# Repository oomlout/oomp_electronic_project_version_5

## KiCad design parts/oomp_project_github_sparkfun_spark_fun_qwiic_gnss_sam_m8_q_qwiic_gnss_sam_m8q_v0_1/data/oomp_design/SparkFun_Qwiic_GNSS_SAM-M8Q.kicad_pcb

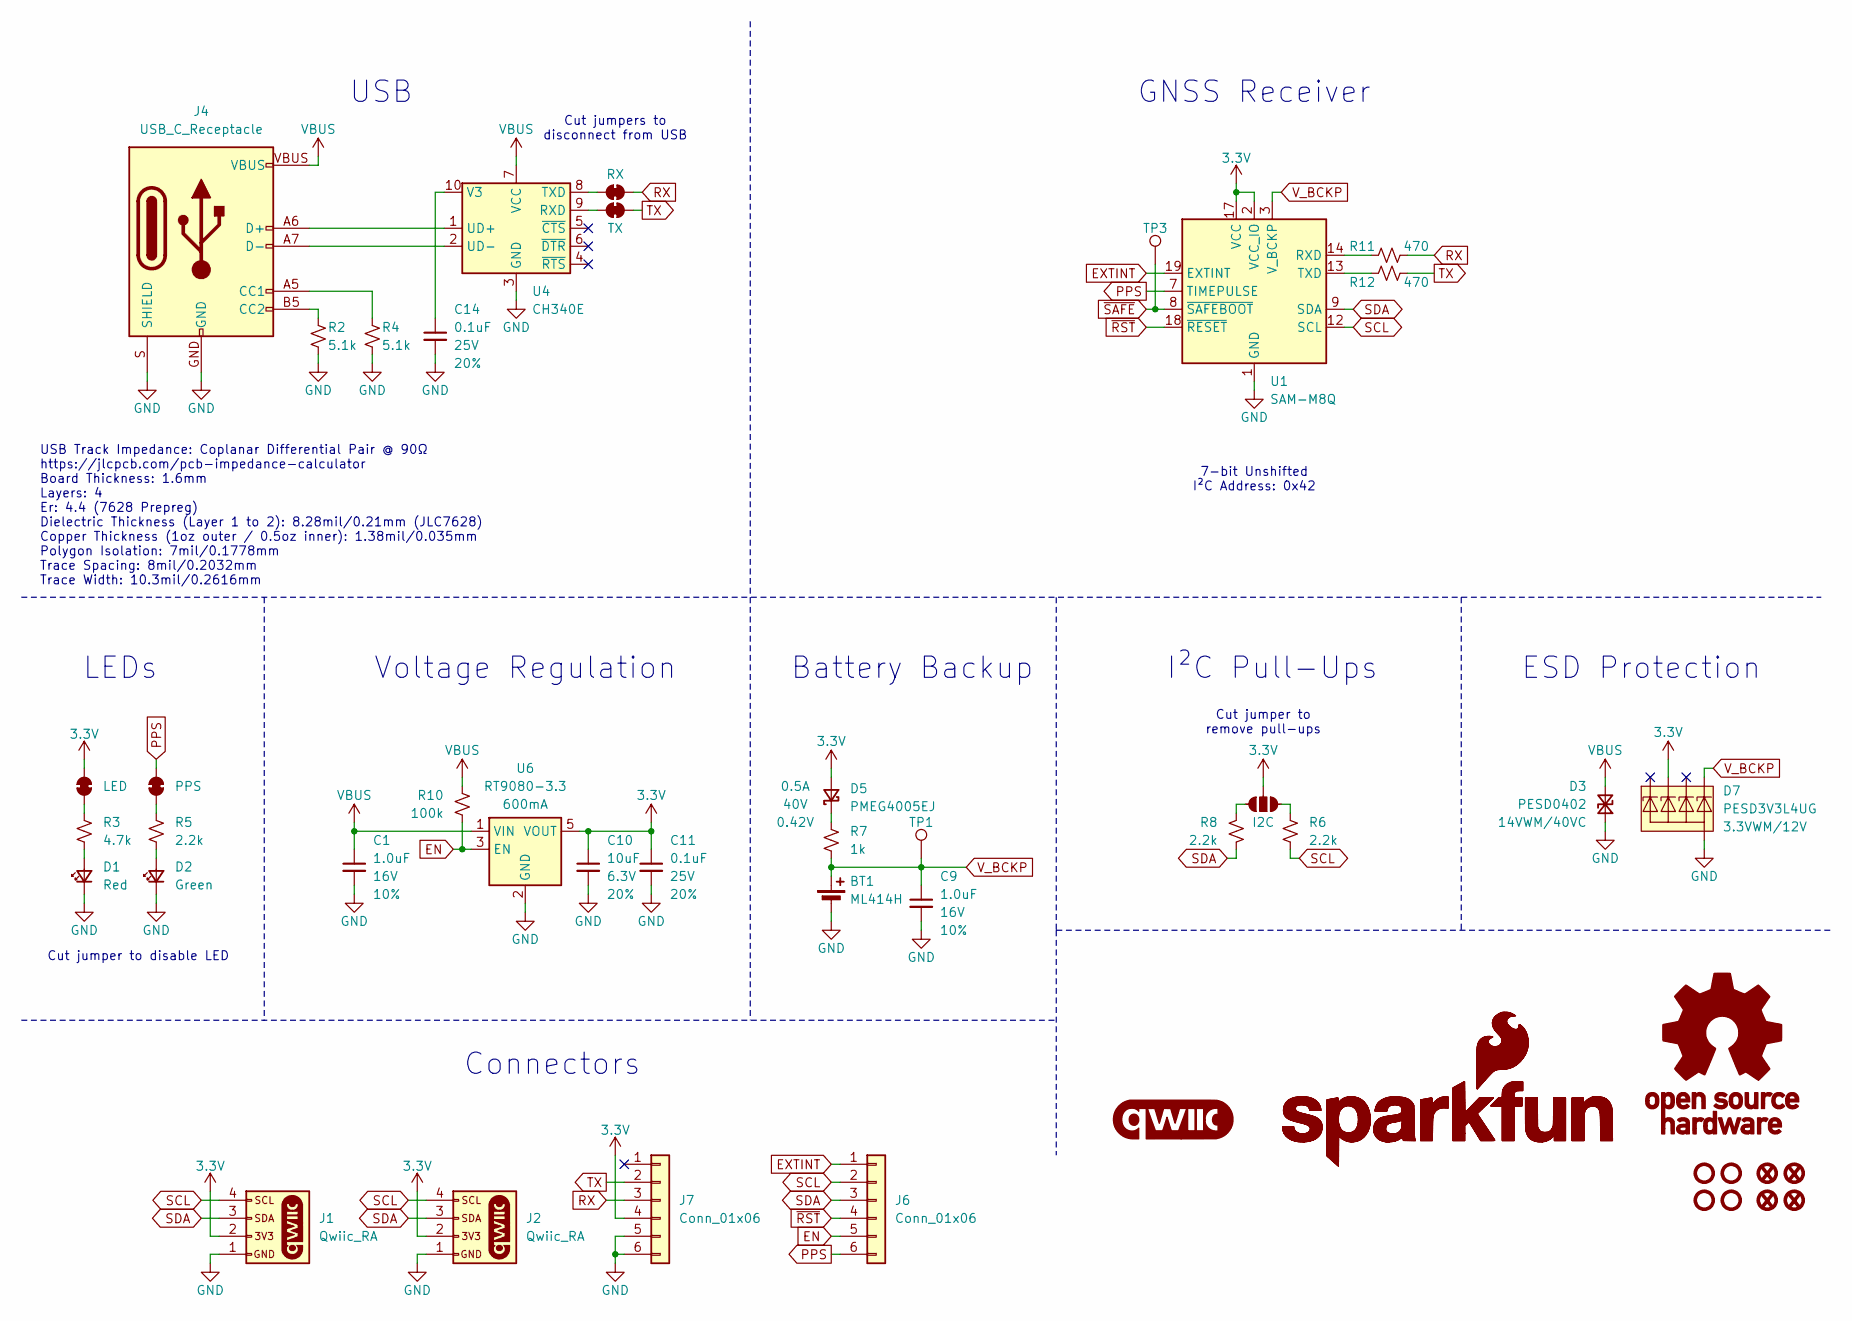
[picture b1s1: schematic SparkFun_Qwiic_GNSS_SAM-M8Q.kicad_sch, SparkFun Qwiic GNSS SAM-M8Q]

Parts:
BT1: ML414H; ML414H_IV01E
C1, C9: 1.0uF; C_0603_1608Metric; Voltage 16V; Tolerance 10%
C10: 10uF; C_0603_1608Metric; Voltage 6.3V; Tolerance 20%
C11, C14: 0.1uF; C_0603_1608Metric; Voltage 25V; Tolerance 20%
D1: Red; LED_0603_1608Metric_Red
D2: Green; LED_1206_Bottom_Green
D3: PESD0402; C_0402_1005Metric; Rating 14VWM/40VC
D5: PMEG4005EJ; SOD-323
D7: PESD3V3L4UG; SOT-353; Rating 3.3VWM/12V
FID1, FID2, FID3, FID4: Fiducial_0.5mm; Fiducial_0.5mm_Mask1mm
G1: qwiic_Logo
G2: SparkFun_Logo; SparkFun_Logo_8mm
G3: SparkFun_Logo
G4: OSHW_Logo; Creative_Commons_License
J1, J2: Qwiic_RA; JST_1x04_P1.0mm_Horizontal_SMD
J4: USB_C_Receptacle; USB-C_16
J6, J7: Conn_01x06; 1x06_P2.54mm
JP1: LED; Jumper_2_NC_Trace
JP2: I2C; Jumper_3_NO
JP3: PPS; Jumper_2_NC_Trace
JP4: RX; Jumper_2_NC_Trace
JP5: TX; Jumper_2_NC_Trace
R2, R4: 5.1k; R_0603_1608Metric
R3: 4.7k; R_0603_1608Metric
R5, R6, R8: 2.2k; R_0603_1608Metric
R7: 1k; R_0603_1608Metric
R10: 100k; R_0603_1608Metric
R11, R12: 470; R_0603_1608Metric
ST1, ST2, ST3, ST4: Standoff
TP1: TestPoint_0.75mm; TestPoint-0.75mm
TP3: 0.75mm; TestPoint-0.75mm
U1: SAM-M8Q; u-blox_SAM-M8Q
U4: CH340E; MSOP-10_3x3mm_P0.5mm
U6: RT9080-3.3; SOT23-5

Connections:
3.3V: C10.1, C11.1, D5.2 (A), D7.3 (K2), J1.2, J2.2, J7.4, JP1.2 (B), JP2.2 (B), U1.2 (VCC_IO), U1.17 (VCC), U6.5 (VOUT)
EN: J6.5, R10.1, U6.3 (EN)
EXTINT: J6.1, U1.19 (EXTINT)
GND: BT1.-, C1.2, C9.2, C10.2, C11.2, C14.2, D1.1 (K), D2.1 (K), D3.1 (A1), D7.2 (A), J1.1, J2.1, J4.GND, J4.S (SHIELD), J7.5, J7.6, R2.1, R4.1, U1.1 (GND), U1.4 (GND), U1.5 (GND), U1.6 (GND), U1.10 (GND), U1.11 (GND), U1.15 (GND), U1.16 (GND), U1.20 (GND), U4.3 (GND), U6.2 (GND)
unnamed: D1.2 (A), R3.1
unnamed: D2.2 (A), R5.1
unnamed: D5.1 (K), R7.2
unnamed: J4.A5 (CC1), R4.2
unnamed: J4.B5 (CC2), R2.2
unnamed: JP1.1 (A), R3.2
unnamed: JP2.1 (A), R6.2
unnamed: JP2.3 (C), R8.2
unnamed: JP3.1 (A), R5.2
unnamed: JP4.1 (A), U4.8 (TXD)
unnamed: JP5.1 (A), U4.9 (RXD)
unnamed: R11.1, U1.14 (RXD)
unnamed: R12.1, U1.13 (TXD)
unnamed: J4.A6 (D+), J4.B6 (D+), U4.1 (UD+)
unnamed: J4.A7 (D-), J4.B7 (D-), U4.2 (UD-)
unnamed: C14.1, U4.10 (V3)
PPS: J6.6, JP3.2 (B), U1.7 (TIMEPULSE)
RX: J7.3, JP4.2 (B), R11.2
SCL: J1.4, J2.4, J6.2, R6.1, U1.12 (SCL)
SDA: J1.3, J2.3, J6.3, R8.1, U1.9 (SDA)
TX: J7.2, JP5.2 (B), R12.2
VBUS: C1.1, D3.2 (A2), J4.VBUS, R10.2, U4.7 (VCC), U6.1 (VIN)
V_BCKP: BT1.+, C9.1, D7.5 (K4), R7.1, TP1.1, U1.3 (V_BCKP)
~RST: J6.4, U1.18 (~RESET)
~SAFE: TP3.1, U1.8 (~SAFEBOOT)

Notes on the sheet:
USB Track Impedance: Coplanar Differential Pair @ 90Ω https://jlcpcb.com/pcb-impedance-calculator Board Thickness: 1.6mm Layers: 4 Er: 4.4 (7628 Prepreg) Dielectric Thickness (Layer 1 to 2): 8.28mil/0.21mm (JLC7628) Copper Thickness (1oz outer / 0.5oz inner): 1.38mil/0.035mm Polygon Isolation: 7mil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
USB
Cut jumpers to disconnect from USB
Cut jumper to remove pull-ups
Battery Backup
I²C Pull-Ups
ESD Protection
Voltage Regulation
Cut jumper to disable LED
7-bit Unshifted I²C Address: 0x42
LEDs
Connectors
GNSS Receiver

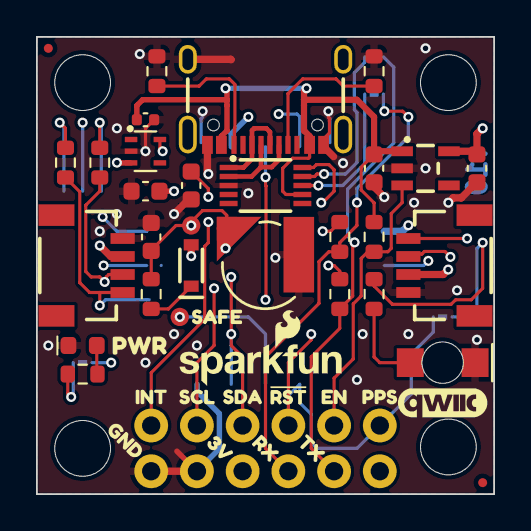
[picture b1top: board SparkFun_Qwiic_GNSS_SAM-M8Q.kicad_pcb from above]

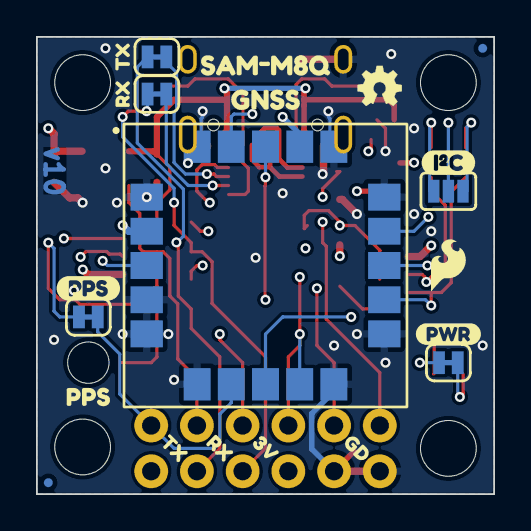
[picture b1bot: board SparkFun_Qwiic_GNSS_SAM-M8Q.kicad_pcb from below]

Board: 4 copper layers, 25.4 x 25.4 mm, 70 parts (21 on the bottom side), 29 nets.

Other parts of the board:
Ref**: Val**; OSHW_Logo_2.5mm
kibuzzard-68A62ADB: G***; kibuzzard-68A62ADB
kibuzzard-68A62B00: G***; kibuzzard-68A62B00
kibuzzard-68A543C0: G***; kibuzzard-68A543C0
kibuzzard-68A543C6: G***; kibuzzard-68A543C6
kibuzzard-68A543D0: G***; kibuzzard-68A543D0
kibuzzard-68A543D8: G***; kibuzzard-68A543D8
kibuzzard-68A5438E: G***; kibuzzard-68A5438E
kibuzzard-68A6334A: G***; kibuzzard-68A6334A
kibuzzard-68B26D79: G***; kibuzzard-68B26D79
kibuzzard-68B65C4A: G***; kibuzzard-68B65C4A
kibuzzard-68B657DC: G***; kibuzzard-68B657DC
kibuzzard-68B657F6: G***; kibuzzard-68B657F6
kibuzzard-68B657FC: G***; kibuzzard-68B657FC
kibuzzard-68B2754E, kibuzzard-68B2754E#2: G***; kibuzzard-68B2754E
kibuzzard-68B2766E: G***; kibuzzard-68B2766E
kibuzzard-68B27525, kibuzzard-68B27525#2: G***; kibuzzard-68B27525
kibuzzard-68B65800: G***; kibuzzard-68B65800
kibuzzard-68B65805: G***; kibuzzard-68B65805
kibuzzard-68F7EB4F: G***; kibuzzard-68F7EB4F
kibuzzard-68F7EE97: G***; kibuzzard-68F7EE97
kibuzzard-68F7EEC6: G***; kibuzzard-68F7EEC6
kibuzzard-68F83B37: G***; kibuzzard-68F83B37

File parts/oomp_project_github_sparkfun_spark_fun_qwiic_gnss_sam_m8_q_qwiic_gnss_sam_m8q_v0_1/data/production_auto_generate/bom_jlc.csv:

Comment,Designator,Footprint,LCSC Part #
0.1uF,"C11,C14",SparkFun-Capacitor:C_0603_1608Metric,C14663
0.75mm,TP3,SparkFun-Connector:TestPoint-1.0mm,
1.0uF,"C1,C9",SparkFun-Capacitor:C_0603_1608Metric,C5673
100k,R10,SparkFun-Resistor:R_0603_1608Metric,C25803
10uF,C10,SparkFun-Capacitor:C_0603_1608Metric,C19702
1k,R7,SparkFun-Resistor:R_0603_1608Metric,C2907002
2.2k,"R5,R6,R8",SparkFun-Resistor:R_0603_1608Metric,C4190
4.7k,R3,SparkFun-Resistor:R_0603_1608Metric,C23162
470,"R11,R12",SparkFun-Resistor:R_0603_1608Metric,C23179
5.1k,"R2,R4",SparkFun-Resistor:R_0603_1608Metric,C23186
CH340E,U4,SparkFun-Semiconductor-Standard:MSOP-10_3x3mm_P0.5mm,
Conn_01x06,"J6,J7",SparkFun-Connector:1x06_P2.54mm,C37208
Green,D2,SparkFun-LED:LED_1206_Bottom_Green,
I2C,JP2,SparkFun-Jumper:Jumper_3_NO,
LED,JP1,SparkFun-Jumper:Jumper_2_NC_Trace,
ML414H,BT1,SparkFun-Battery:ML414H_IV01E,
PESD0402,D3,SparkFun-Capacitor:C_0402_1005Metric,C316059
PESD3V3L4UG,D7,SparkFun-Semiconductor-Standard:SOT-353,C70500
PMEG4005EJ,D5,SparkFun-Semiconductor-Standard:SOD-323,
PPS,JP3,SparkFun-Jumper:Jumper_2_NC_Trace,
Qwiic_RA,"J1,J2",SparkFun-Connector:JST_1x04_P1.0mm_Horizontal_SMD,C160404
Red,D1,SparkFun-LED:LED_0603_1608Metric_Red,
RT9080-3.3,U6,SparkFun-Semiconductor-Standard:SOT23-5,
RX,JP4,SparkFun-Jumper:Jumper_2_NC_Trace,
SAM-M8Q,U1,SparkFun-GNSS:u-blox_SAM-M8Q,
TestPoint_0.75mm,TP1,SparkFun-Connector:TestPoint-1.0mm,
TX,JP5,SparkFun-Jumper:Jumper_2_NC_Trace,
USB_C_Receptacle,J4,SparkFun-Connector:USB-C_16,C2765186

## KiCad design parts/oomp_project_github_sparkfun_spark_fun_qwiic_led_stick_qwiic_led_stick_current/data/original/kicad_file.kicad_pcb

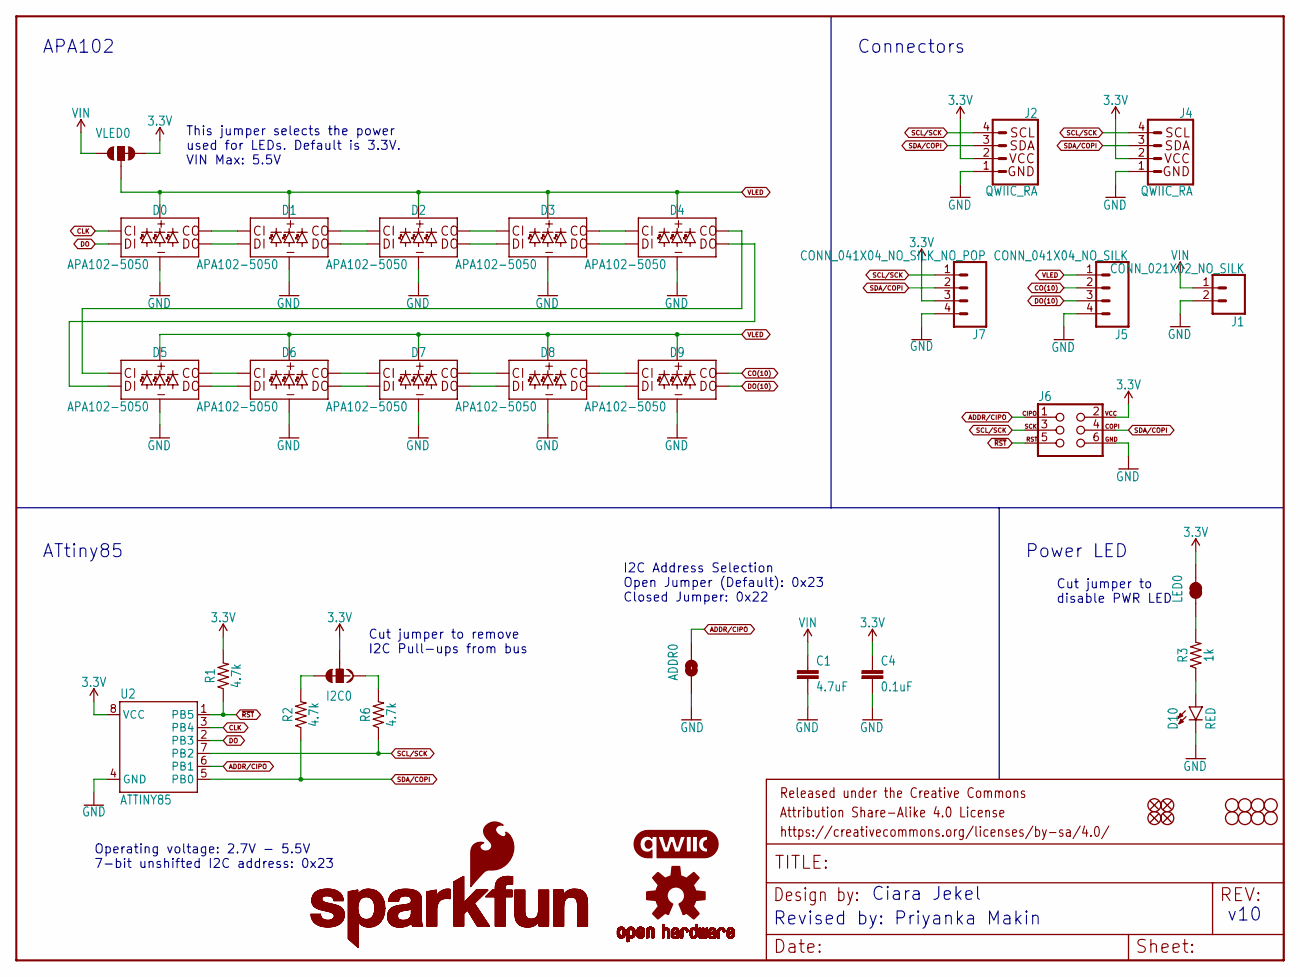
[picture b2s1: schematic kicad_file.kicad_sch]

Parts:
ADDR0: JUMPER-SMT_2_NO_SILK; SMT-JUMPER_2_NO_SILK
C1: 4.7uF; 0603
C4: 0.1uF; 0603
D0, D1, D2, D3, D4, D5, D6, D7, D8, D9: APA102-5050
D10: RED; LED-0603
FRAME1: FRAME-LETTER; CREATIVE_COMMONS
H1, H2, H3, H4: STAND-OFF
I2C0: JUMPER-SMT_3_2-NC_TRACE_SILK; SMT-JUMPER_3_2-NC_TRACE_SILK
J1: CONN_021X02_NO_SILK; 1X02_NO_SILK
J2, J4: QWIIC_RA; JST04_1MM_RA
J5: CONN_041X04_NO_SILK; 1X04_NO_SILK
J6: AVR_SPI_PROG_3X2TESTPOINTS; 2X3_TEST_POINTS
J7: CONN_041X04_NO_SILK_NO_POP; 1X04_NO_SILK
JP1, JP2, JP5, JP6: FIDUCIALUFIDUCIAL; FIDUCIAL-MICRO
JP3, JP4, JP7, JP8: STAND-OFF
LED0: JUMPER-SMT_2_NC_TRACE_SILK; SMT-JUMPER_2_NC_TRACE_SILK
LOGO1: OSHW-LOGOMINI; OSHW-LOGO-MINI
LOGO2, LOGO5: SFE_LOGO_NAME.2_INCH; SFE_LOGO_NAME_.2
LOGO3: QWIIC_LOGO_5MM; QWIIC_5MM
LOGO4: SFE_LOGO_FLAME.2_INCH; SFE_LOGO_FLAME_.2
R1, R2, R6: 4.7k; 0603
R3: 1k; 0603
U2: ATTINY85
VLED0: JUMPER-SMT_3_1-NC_TRACE_SILK; SMT-JUMPER_3_1-NC_TRACE_SILK

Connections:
3.3V: C4.1, I2C0.2, J2.2, J4.2, J6.2, J7.3, LED0.2, R1.2, U2.8 (VCC), VLED0.3
ADDR/CIPO: ADDR0.2, J6.1, U2.6 (PB1)
CLK: D0.P2 (CI), U2.3 (PB4)
CO(10): D9.P5 (CO), J5.2
DO: D0.P1 (DI), U2.2 (PB3)
DO(10): D9.P6 (DO), J5.3
GND: ADDR0.1, C1.2, C4.2, D0.P3 (GND), D1.P3 (GND), D2.P3 (GND), D3.P3 (GND), D4.P3 (GND), D5.P3 (GND), D6.P3 (GND), D7.P3 (GND), D8.P3 (GND), D9.P3 (GND), D10.C, J1.2, J2.1, J4.1, J5.4, J6.6, J7.4, U2.4 (GND)
unnamed: D10.A, R3.1
unnamed: LED0.1, R3.2
unnamed: I2C0.3, R2.2
unnamed: I2C0.1, R6.2
unnamed: D8.P6 (DO), D9.P1 (DI)
unnamed: D8.P5 (CO), D9.P2 (CI)
unnamed: D7.P5 (CO), D8.P2 (CI)
unnamed: D7.P6 (DO), D8.P1 (DI)
unnamed: D6.P5 (CO), D7.P2 (CI)
unnamed: D6.P6 (DO), D7.P1 (DI)
unnamed: D5.P5 (CO), D6.P2 (CI)
unnamed: D5.P6 (DO), D6.P1 (DI)
unnamed: D4.P5 (CO), D5.P2 (CI)
unnamed: D4.P6 (DO), D5.P1 (DI)
unnamed: D3.P5 (CO), D4.P2 (CI)
unnamed: D3.P6 (DO), D4.P1 (DI)
unnamed: D2.P6 (DO), D3.P1 (DI)
unnamed: D2.P5 (CO), D3.P2 (CI)
unnamed: D1.P6 (DO), D2.P1 (DI)
unnamed: D1.P5 (CO), D2.P2 (CI)
unnamed: D0.P5 (CO), D1.P2 (CI)
unnamed: D0.P6 (DO), D1.P1 (DI)
SCL/SCK: J2.4, J4.4, J6.3, J7.1, R6.1, U2.7 (PB2)
SDA/COPI: J2.3, J4.3, J6.4, J7.2, R2.1, U2.5 (PB0)
VIN: C1.1, J1.1, VLED0.1
VLED: D0.P4 (VCC), D1.P4 (VCC), D2.P4 (VCC), D3.P4 (VCC), D4.P4 (VCC), D5.P4 (VCC), D6.P4 (VCC), D7.P4 (VCC), D8.P4 (VCC), D9.P4 (VCC), J5.1, VLED0.2
~RST: J6.5, R1.1, U2.1 (PB5)

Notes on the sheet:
APA102
Cut jumper to disable PWR LED
v10
Cut jumper to remove I2C Pull-ups from bus
I2C Address Selection Open Jumper (Default): 0x23 Closed Jumper: 0x22
This jumper selects the power used for LEDs. Default is 3.3V. VIN Max: 5.5V
Power LED
Revised by: Priyanka Makin
Ciara Jekel
Connectors
ATtiny85
Operating voltage: 2.7V - 5.5V 7-bit unshifted I2C address: 0x23

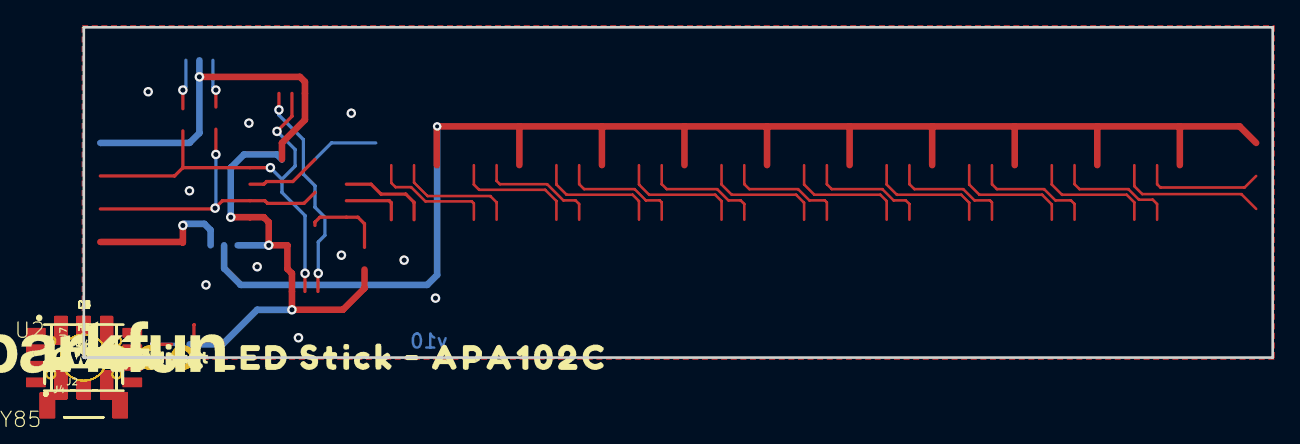
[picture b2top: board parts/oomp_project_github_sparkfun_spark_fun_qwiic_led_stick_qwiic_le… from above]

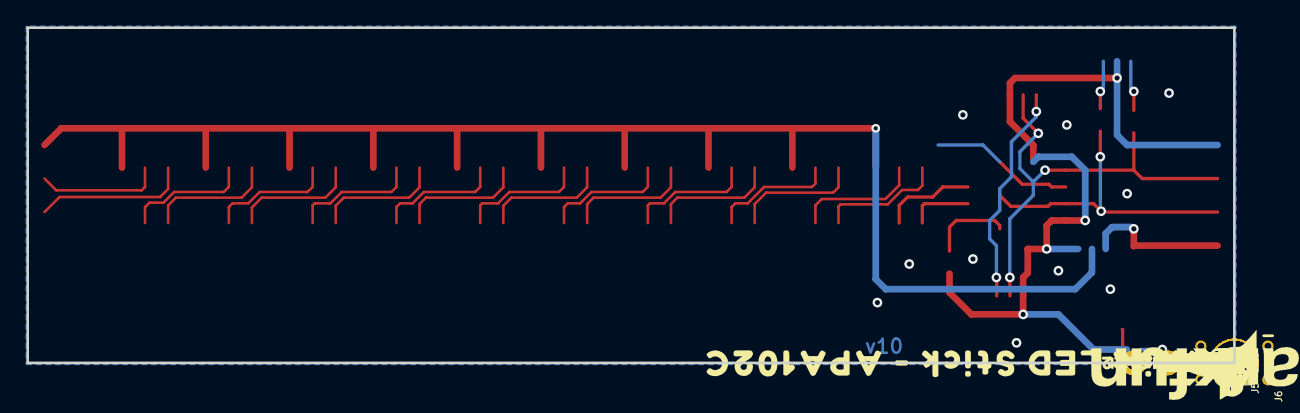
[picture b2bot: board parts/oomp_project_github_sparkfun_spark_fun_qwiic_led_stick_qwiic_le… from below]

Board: 2 copper layers, 91.4 x 25.4 mm, 93 parts (35 on the bottom side), 34 nets.

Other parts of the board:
U$1, U$2, U$3, U$4, U$5, U$8: #GND#0
U$6: #CO#0
U$7: #DO#0
U$9, U$12: #VLED#0
U$10: #ADDR#0
U$11: (I_SUPER2_C)
U$14, U$17: #3#3V#0
U$15: #_DO#0
U$16: #_CO#0
U$18, U$19: #VIN#0
U$20: #SDA#0
U$21: #SDA_#0
U$22: #SCL#0
U$23: #SCL_#0
U$24: #LED#0
U$25: #3#3V#1
U$26: PWR0
U$28: VLED0
U$29: #VIN#4
U$30, U$47: QWIIC_MOUNT5
U$31: 00
U$32: 10
U$33: 20
U$34: 30
U$35: 40
U$36: 50
U$37: 60
U$38: 70
U$39: 80
U$40: 90
U$41: RED0
U$42: BLUE0
U$43: GREEN0
U$44: YELLOW0
U$45: OPEN#_0X230
U$46: CLOSED#_0X220
U$48, U$49: QWIIC_LED_STICK_#_APA102C0

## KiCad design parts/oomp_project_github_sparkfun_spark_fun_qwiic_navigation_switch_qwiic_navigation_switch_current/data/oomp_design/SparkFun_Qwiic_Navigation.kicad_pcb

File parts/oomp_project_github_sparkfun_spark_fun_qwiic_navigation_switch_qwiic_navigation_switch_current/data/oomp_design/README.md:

# OOMP KiCad design copy

Open `SparkFun_Qwiic_Navigation.kicad_pro` (or the `.kicad_pcb` / `.kicad_sch`) in KiCad. Local OOMP libraries are under `libraries/`. Original inputs are preserved in [../original/](../original/).

Only verified unchanged installed KiCad defaults were renamed. Modified, custom, unmatched and unavailable items remain unchanged. Soldering variants are never swapped during conversion. Existing pad coordinates, nets and UUIDs are preserved.

See [conversion_report.yaml](conversion_report.yaml) for every conversion and skip. Copy this directory before editing; regeneration refuses to overwrite edited design files.

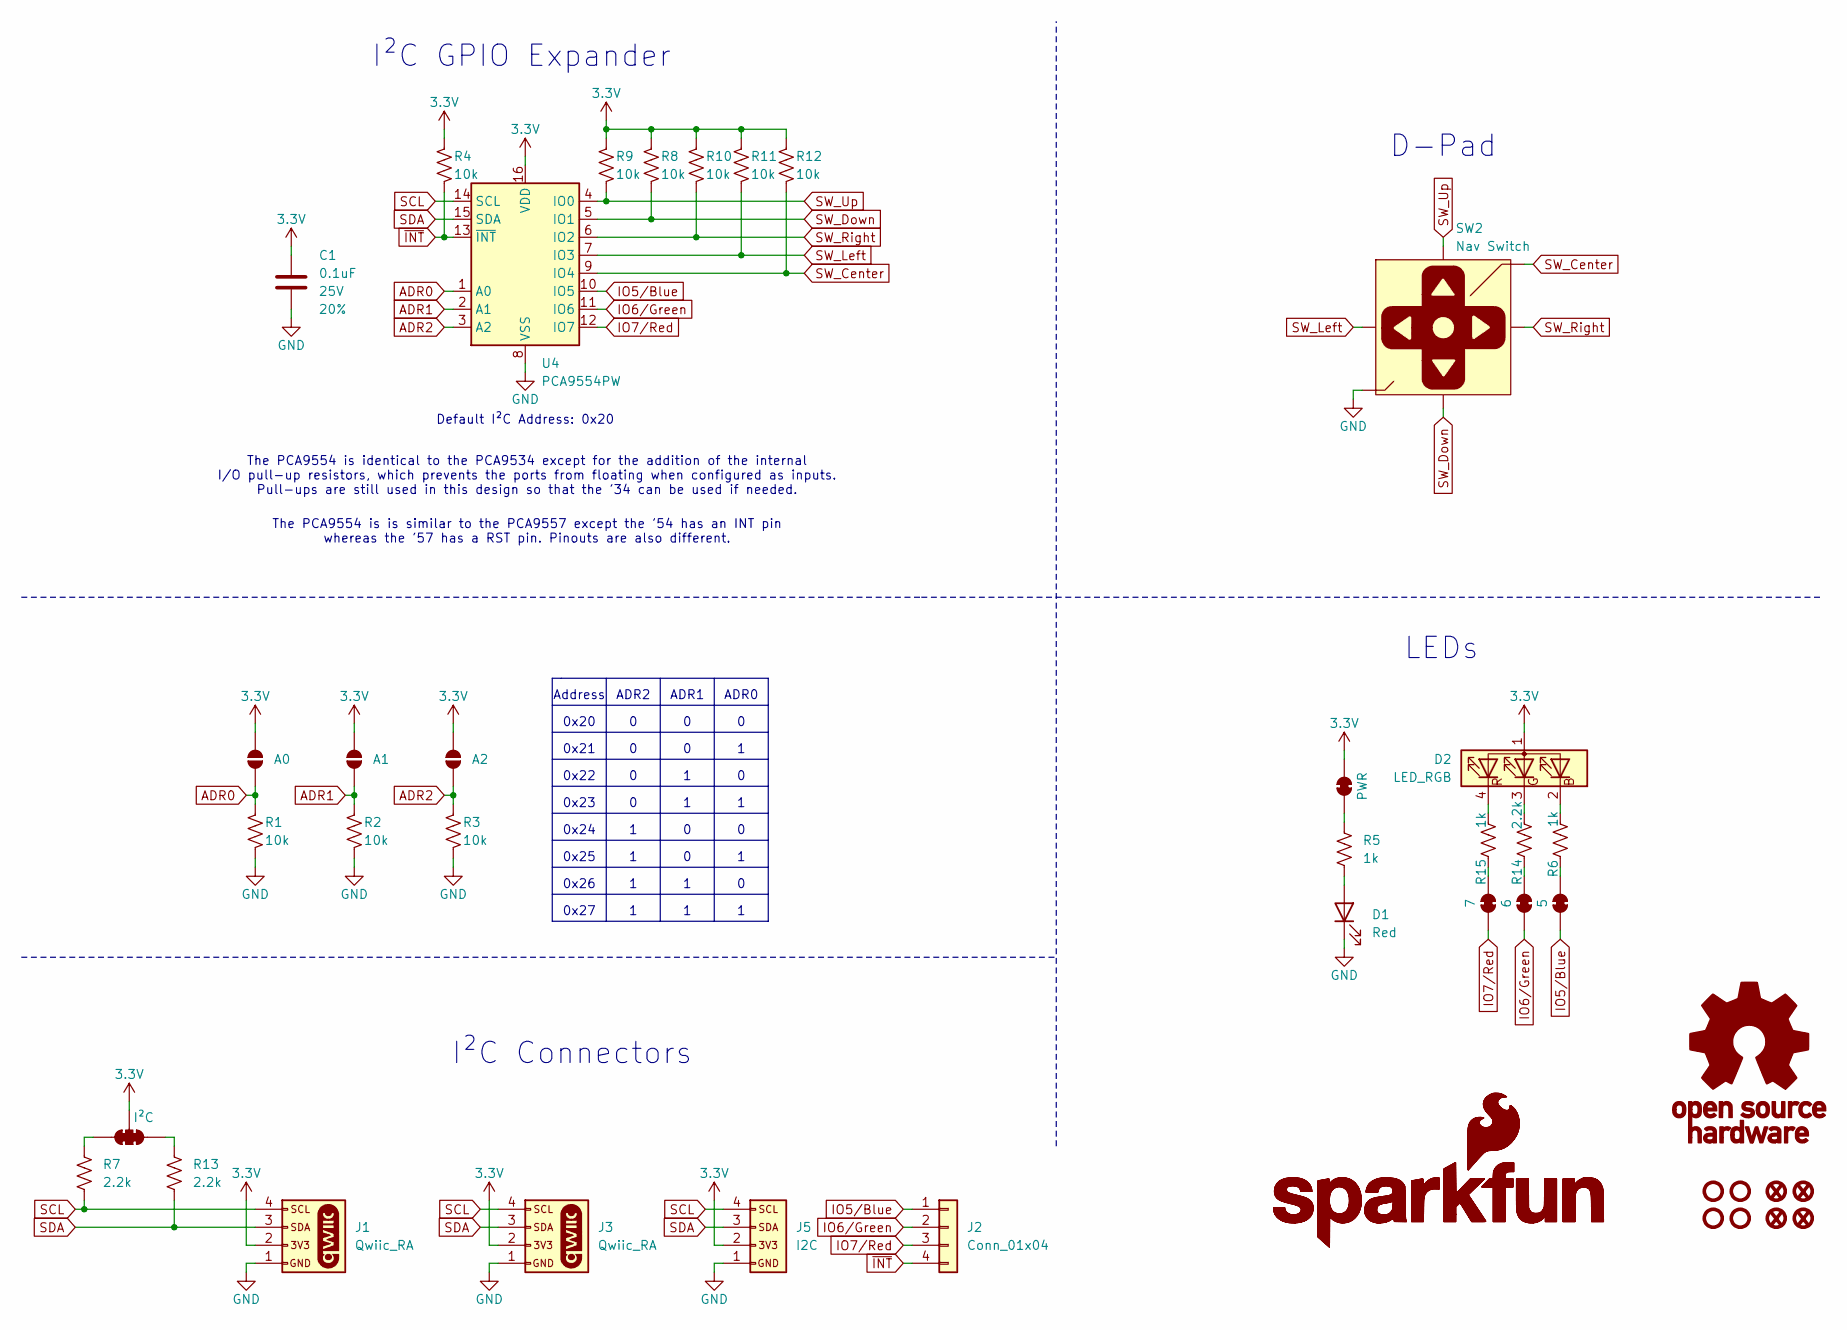
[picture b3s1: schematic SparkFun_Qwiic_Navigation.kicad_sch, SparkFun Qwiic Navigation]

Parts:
C1: 0.1uF; C_0603_1608Metric; Voltage 25V; Tolerance 20%
D1: Red; LED_0603_1608Metric_Red
D2: LED_RGB; LED_1205_RGB_Bottom
FID1, FID2, FID3, FID4: Fiducial_0.5mm; Fiducial_0.5mm_Mask1mm
G1: OSHW_Logo; Creative_Commons_License
G3: SparkFun_Logo
G5: SparkFun_Logo; SparkFun_Logo_8mm
J1, J3: Qwiic_RA; JST_SMD_1.0mm-4_RA
J2: Conn_01x04; 1x04
J5: I2C; 1x04
JP1: A0; Jumper_2_NO
JP2: A1; Jumper_2_NO
JP3: A2; Jumper_2_NO
JP4: PWR; Jumper_2_NC_Trace
JP5: 5; Jumper_2_NC_Trace
JP6: I²C; Jumper_3_NC-2_Trace
JP7: 6; Jumper_2_NC_Trace
JP8: 7; Jumper_2_NC_Trace
R1, R2, R3, R4, R8, R9, R10, R11, R12: 10k; R_0603_1608Metric
R5, R6, R15: 1k; R_0603_1608Metric
R7, R13, R14: 2.2k; R_0603_1608Metric
ST1, ST2, ST3, ST4: Standoff
SW2: Nav Switch; Navigation_SMD_7.5x7.5mm
U4: PCA9554PW; TSSOP-16_4.4x5mm_P0.65mm

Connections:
3.3V: C1.1, D2.1 (A), J1.2, J3.2, J5.2, JP1.2 (B), JP2.2 (B), JP3.2 (B), JP4.2 (B), JP6.2 (C), R4.2, R8.2, R9.2, R10.2, R11.2, R12.2, U4.16 (VDD)
ADR0: JP1.1 (A), R1.2, U4.1 (A0)
ADR1: JP2.1 (A), R2.2, U4.2 (A1)
ADR2: JP3.1 (A), R3.2, U4.3 (A2)
GND: C1.2, D1.1 (K), J1.1, J3.1, J5.1, R1.1, R2.1, R3.1, SW2.2 (GND), U4.8 (VSS)
IO5/Blue: J2.1, JP5.2 (B), U4.10 (IO5)
IO6/Green: J2.2, JP7.2 (B), U4.11 (IO6)
IO7/Red: J2.3, JP8.2 (B), U4.12 (IO7)
unnamed: D1.2 (A), R5.2
unnamed: D2.2 (BK), R6.2
unnamed: D2.3 (GK), R14.2
unnamed: D2.4 (RK), R15.2
unnamed: JP4.1 (A), R5.1
unnamed: JP5.1 (A), R6.1
unnamed: JP6.1 (A), R13.1
unnamed: JP6.3 (B), R7.1
unnamed: JP7.1 (A), R14.1
unnamed: JP8.1 (A), R15.1
SCL: J1.4, J3.4, J5.4, R7.2, U4.14 (SCL)
SDA: J1.3, J3.3, J5.3, R13.2, U4.15 (SDA)
SW_Center: R12.1, SW2.5 (Center), U4.9 (IO4)
SW_Down: R8.1, SW2.3 (Down), U4.5 (IO1)
SW_Left: R11.1, SW2.1 (Left), U4.7 (IO3)
SW_Right: R10.1, SW2.4 (Right), U4.6 (IO2)
SW_Up: R9.1, SW2.6 (Up), U4.4 (IO0)
~INT: J2.4, R4.1, U4.13 (~INT)

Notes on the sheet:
The PCA9554 is is similar to the PCA9557 except the '54 has an INT pin whereas the '57 has a RST pin. Pinouts are also different.
Default I²C Address: 0x20
I²C GPIO Expander
0x20
I²C Connectors
ADR2
ADR0
0x23
The PCA9554 is identical to the PCA9534 except for the addition of the internal I/O pull-up resistors, which prevents the ports from floating when configured as inputs. Pull-ups are still used in this design so that the '34 can be used if needed.
0x22
LEDs
0x25
0x26
0x24
D-Pad
0x27
ADR1
0x21
Address

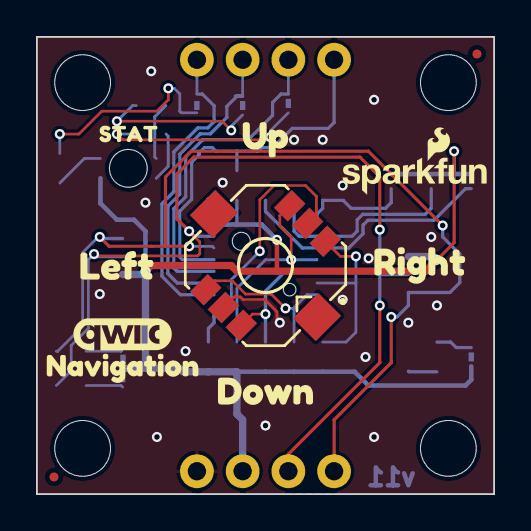
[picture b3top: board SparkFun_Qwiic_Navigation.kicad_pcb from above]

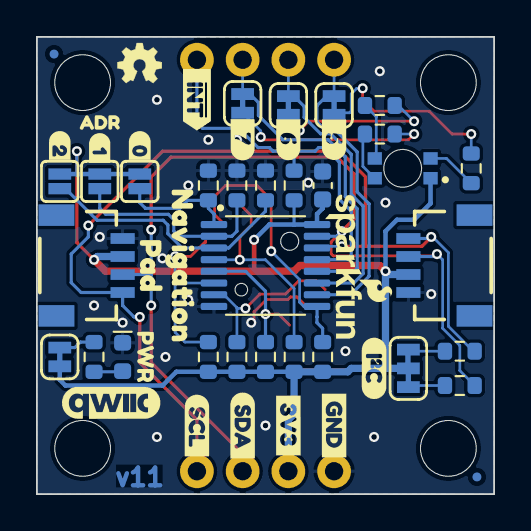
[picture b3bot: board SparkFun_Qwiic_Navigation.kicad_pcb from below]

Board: 2 copper layers, 25.4 x 25.4 mm, 64 parts (48 on the bottom side), 26 nets.

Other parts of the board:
Ref**: Val**; OSHW_Logo_2.5mm
kibuzzard-64C2E6A3: G***; kibuzzard-64C2E6A3
kibuzzard-66EED5D2: G***; kibuzzard-66EED5D2
kibuzzard-66EF6B89: G***; kibuzzard-66EF6B89
kibuzzard-66EF7A0B: G***; kibuzzard-66EF7A0B
kibuzzard-66EF7A03: G***; kibuzzard-66EF7A03
kibuzzard-66EF7A24: G***; kibuzzard-66EF7A24
kibuzzard-66EF7AE6: G***; kibuzzard-66EF7AE6
kibuzzard-66EF7AEF: G***; kibuzzard-66EF7AEF
kibuzzard-66EF7B1E: G***; kibuzzard-66EF7B1E
kibuzzard-66EF7B7C: G***; kibuzzard-66EF7B7C
kibuzzard-66EF7B15: G***; kibuzzard-66EF7B15
kibuzzard-66EF55AC: G***; kibuzzard-66EF55AC
kibuzzard-66EF79E9: G***; kibuzzard-66EF79E9
kibuzzard-66EF559E: G***; kibuzzard-66EF559E
kibuzzard-66EF5597: G***; kibuzzard-66EF5597
kibuzzard-66F18F5E: G***; kibuzzard-66F18F5E
kibuzzard-66F18F8F: G***; kibuzzard-66F18F8F
kibuzzard-66F18F9B: G***; kibuzzard-66F18F9B
kibuzzard-66F182A6: G***; kibuzzard-66F182A6
kibuzzard-675B45F7: G***; kibuzzard-675B45F7
kibuzzard-67117BDD: G***; kibuzzard-67117BDD
kibuzzard-6730262A: G***; kibuzzard-6730262A

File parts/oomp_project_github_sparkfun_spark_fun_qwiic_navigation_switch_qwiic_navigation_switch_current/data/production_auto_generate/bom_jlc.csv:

Comment,Designator,Footprint,LCSC Part #
0.1uF,C1,SparkFun-Capacitor:C_0603_1608Metric,C14663
10k,"R1,R2,R3,R4,R8,R9,R10,R11,R12",SparkFun-Resistor:R_0603_1608Metric,C98220
1k,"R5,R6,R15",SparkFun-Resistor:R_0603_1608Metric,C2907002
2.2k,"R7,R13,R14",SparkFun-Resistor:R_0603_1608Metric,C4190
5,JP5,SparkFun-Jumper:Jumper_2_NC_Trace,
6,JP7,SparkFun-Jumper:Jumper_2_NC_Trace,
7,JP8,SparkFun-Jumper:Jumper_2_NC_Trace,
A0,JP1,SparkFun-Jumper:Jumper_2_NO,
A1,JP2,SparkFun-Jumper:Jumper_2_NO,
A2,JP3,SparkFun-Jumper:Jumper_2_NO,
Conn_01x04,J2,SparkFun-Connector:1x04,C42431795
I2C,J5,SparkFun-Connector:1x04,C42431795
I²C,JP6,SparkFun-Jumper:Jumper_3_NC-2_Trace,
LED_RGB,D2,SparkFun-LED:LED_1205_RGB_Bottom,
Nav Switch,SW2,SparkFun-Switch:Navigation_SMD_7.5x7.5mm,
PCA9554PW,U4,SparkFun-Semiconductor-Standard:TSSOP-16_4.4x5mm_P0.65mm,
PWR,JP4,SparkFun-Jumper:Jumper_2_NC_Trace,
Qwiic_RA,"J1,J3",SparkFun-Connector:JST_SMD_1.0mm-4_RA,C160404
Red,D1,SparkFun-LED:LED_0603_1608Metric_Red,

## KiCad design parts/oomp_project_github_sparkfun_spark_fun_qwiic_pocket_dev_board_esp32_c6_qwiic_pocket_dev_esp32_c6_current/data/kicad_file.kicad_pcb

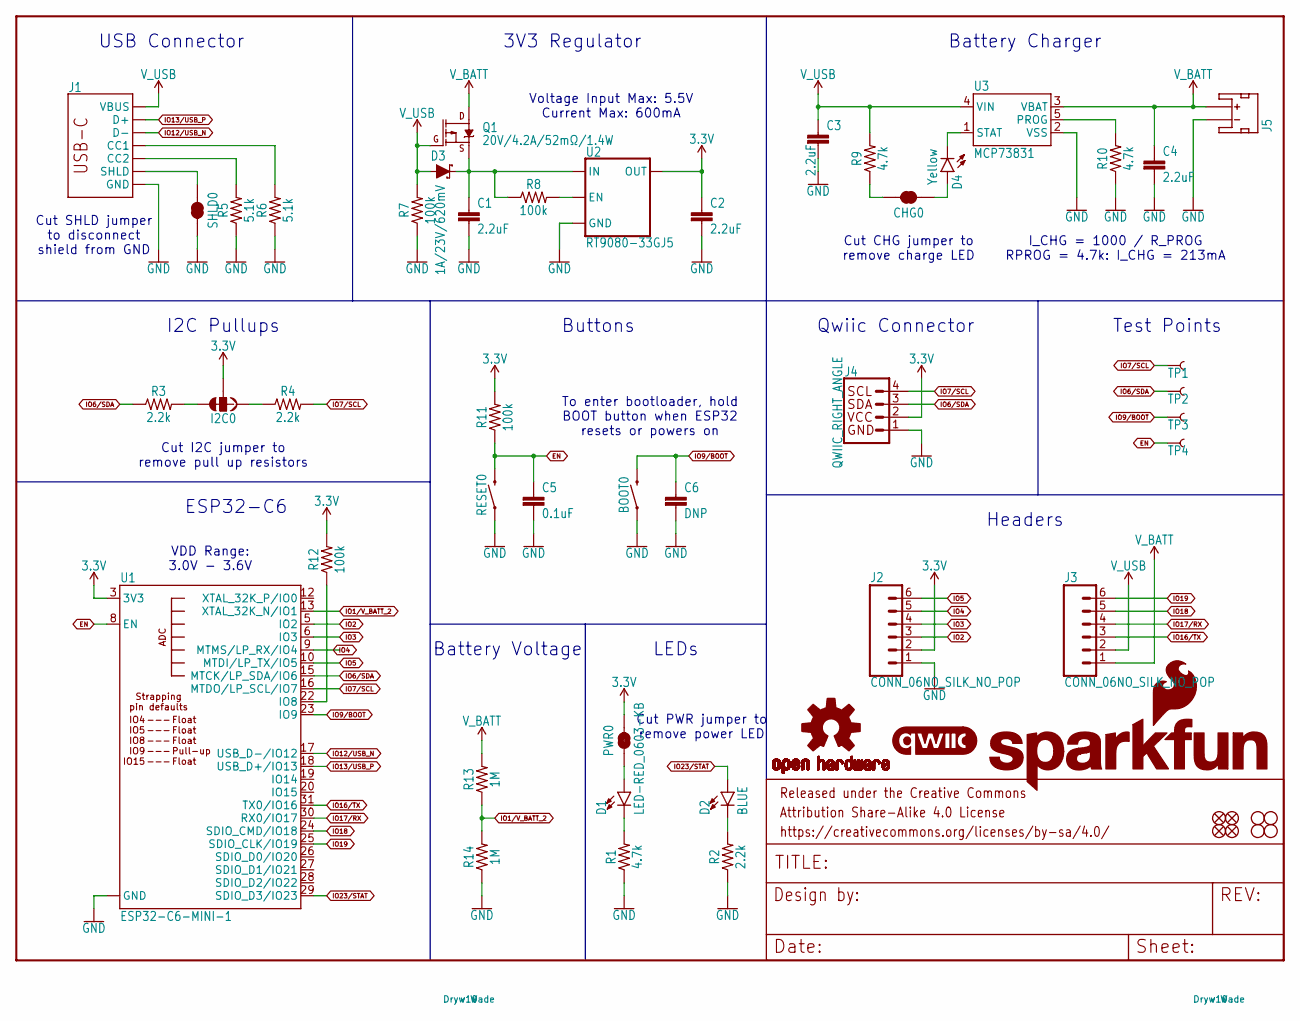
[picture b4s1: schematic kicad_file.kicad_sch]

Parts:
BOOT0: MOMENTARY-SWITCH-SPST-SMD-4.6X2.8MM; TACTILE_SWITCH_SMD_4.6X2.8MM
C1, C2, C3, C4: 2.2uF; 0402-TIGHT
C5: 0.1uF; 0402-TIGHT
C6: DNP; 0402-TIGHT
CHG0: JUMPER-SMT_2_NC_TRACE_SILK; SMT-JUMPER_2_NC_TRACE_SILK
D1: LED-RED_0603-KB; LED-0603
D2: BLUE; LED-0603
D3: 1A/23V/620mV; SOD-323
D4: Yellow; LED-0603
FD1, FD2, FD3, FD4: FIDUCIALUFIDUCIAL; FIDUCIAL-MICRO
FRAME1: FRAME-LETTER; CREATIVE_COMMONS
H1, H2, H3, H4: STAND-OFF
I2C0: JUMPER-SMT_3_2-NC_TRACE_SILK; SMT-JUMPER_3_2-NC_TRACE_SILK
J1: USB Female Type C Connector; USB-C-16P_4LAYER-PADS
J2, J3: CONN_06NO_SILK_NO_POP; 1X06_NO_SILK
J4: QWIIC_RIGHT_ANGLE; JST04_1MM_RA
J5: JST_2MM_MALE; JST-2-SMD
LOGO1: SFE_LOGO_NAME_FLAMEBLANK; BLANK
LOGO2: OSHW-LOGOS; OSHW-LOGO-S
LOGO3: QWIIC_LOGO_3MM; QWIIC_3MM
PWR0: JUMPER-SMT_2_NC_TRACE_SILK; SMT-JUMPER_2_NC_TRACE_SILK
Q1: 20V/4.2A/52mΩ/1.4W; SOT23-3
R1, R9, R10: 4.7k; 0402-TIGHT
R2, R3, R4: 2.2k; 0402-TIGHT
R5, R6: 5.1k; 0402-TIGHT
R7, R8, R11, R12: 100k; 0402-TIGHT
R13, R14: 1M; 0402-TIGHT
RESET0: MOMENTARY-SWITCH-SPST-SMD-4.6X2.8MM; TACTILE_SWITCH_SMD_4.6X2.8MM
SHLD0: JUMPER-SMT_2_NC_TRACE_SILK; SMT-JUMPER_2_NC_TRACE_SILK
TP1, TP2, TP3, TP4: TEST-POINT3; PAD.03X.03
U1: ESP32-C6-MINI-1
U2: RT9080-33GJ5; SOT23-5
U3: MCP73831; SOT23-5

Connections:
3.3V: C2.1, I2C0.2, J2.2, J4.2, PWR0.2, R11.2, R12.2, U1.3 (3V3), U2.5 (OUT)
EN: C5.1, R11.1, RESET0.3 (2), RESET0.4 (2), TP4.1, U1.8 (EN)
GND: BOOT0.1, BOOT0.2 (1), C1.2, C2.2, C3.2, C4.2, C5.2, C6.2, J1.GND, J1.GND2 (GND), J2.1, J4.1, J5.1 (-), R1.1, R2.1, R5.1, R6.1, R7.1, R10.1, R14.1, RESET0.1, RESET0.2 (1), SHLD0.2, U1.1 (GND), U1.2 (GND), U1.11 (GND), U1.14 (GND), U1.36 (GND), U1.37 (GND), U1.38 (GND), U1.39 (GND), U1.40 (GND), U1.41 (GND), U1.42 (GND), U1.43 (GND), U1.44 (GND), U1.45 (GND), U1.46 (GND), U1.47 (GND), U1.48 (GND), U1.49.1 (GND), U1.49.2 (GND), U1.49.3 (GND), U1.49.4 (GND), U1.49.5 (GND), U1.49.6 (GND), U1.49.7 (GND), U1.49.8 (GND), U1.49.9 (GND), U1.50 (GND), U1.51 (GND), U1.52 (GND), U1.53 (GND), U2.2 (GND), U3.2 (VSS)
IO1/V_BATT_2: R13.1, R14.2, U1.13 (XTAL_32K_N/IO1)
IO2: J2.3, U1.5 (IO2)
IO3: J2.4, U1.6 (IO3)
IO4: J2.5, U1.9 (MTMS/LP_RX/IO4)
IO5: J2.6, U1.10 (MTDI/LP_TX/IO5)
IO6/SDA: J4.3, R3.1, TP2.1, U1.15 (MTCK/LP_SDA/IO6)
IO7/SCL: J4.4, R4.2, TP1.1, U1.16 (MTDO/LP_SCL/IO7)
IO9/BOOT: BOOT0.3 (2), BOOT0.4 (2), C6.1, TP3.1, U1.23 (IO9)
IO12/USB_N: J1.A7 (D-), J1.B7 (D-), U1.17 (USB_D-/IO12)
IO13/USB_P: J1.A6 (D+), J1.B6 (D+), U1.18 (USB_D+/IO13)
IO16/TX: J3.3, U1.31 (TX0/IO16)
IO17/RX: J3.4, U1.30 (RX0/IO17)
IO18: J3.5, U1.24 (SDIO_CMD/IO18)
IO19: J3.6, U1.25 (SDIO_CLK/IO19)
IO23/STAT: D2.A, U1.29 (SDIO_D3/IO23)
unnamed: D1.C, R1.2
unnamed: D1.A, PWR0.1
unnamed: D2.C, R2.2
unnamed: I2C0.3, R3.2
unnamed: I2C0.1, R4.1
unnamed: R8.2, U2.3 (EN)
unnamed: J1.B5 (CC2), R5.2
unnamed: J1.A5 (CC1), R6.2
unnamed: C1.1, D3.C, Q1.2 (S), R8.1, U2.1 (IN)
unnamed: D4.C, U3.1 (STAT)
unnamed: CHG0.1, D4.A
unnamed: CHG0.2, R9.1
unnamed: R10.2, U3.5 (PROG)
unnamed: R12.1, U1.22 (IO8)
SHLD: J1.SHLD1 (SHLD), J1.SHLD2 (SHLD), J1.SHLD3 (SHLD), J1.SHLD4 (SHLD), SHLD0.1
V_BATT: C4.1, J3.1, J5.2 (+), Q1.3 (D), R13.2, U3.3 (VBAT)
V_USB: C3.1, D3.A, J1.VBUS1 (VBUS), J1.VBUS2 (VBUS), J3.2, Q1.1 (G), R7.2, R9.2, U3.4 (VIN)

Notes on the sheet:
Cut I2C jumper to remove pull up resistors
I_CHG = 1000 / R_PROG RPROG = 4.7k: I_CHG = 213mA
Test Points
ESP32-C6
Battery Charger
Cut SHLD jumper to disconnect shield from GND
Buttons
3V3 Regulator
Qwiic Connector
Cut PWR jumper to remove power LED
VDD Range: 3.0V - 3.6V
I2C Pullups
USB Connector
Battery Voltage
Voltage Input Max: 5.5V Current Max: 600mA
Headers
To enter bootloader, hold BOOT button when ESP32 resets or powers on
Cut CHG jumper to remove charge LED
LEDs

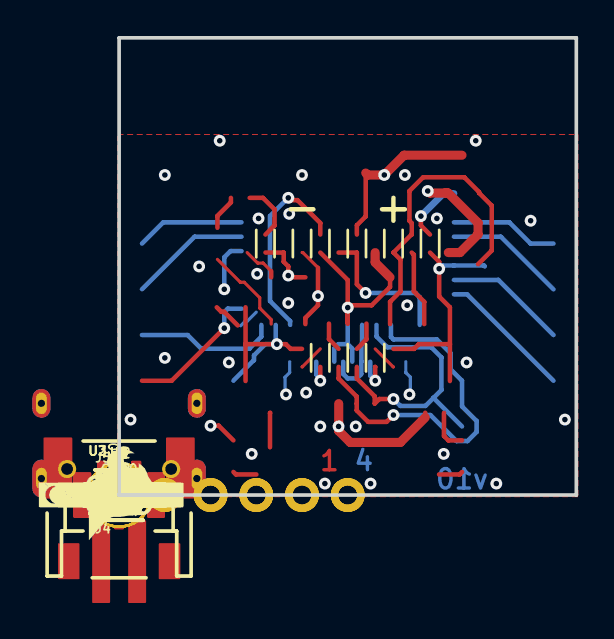
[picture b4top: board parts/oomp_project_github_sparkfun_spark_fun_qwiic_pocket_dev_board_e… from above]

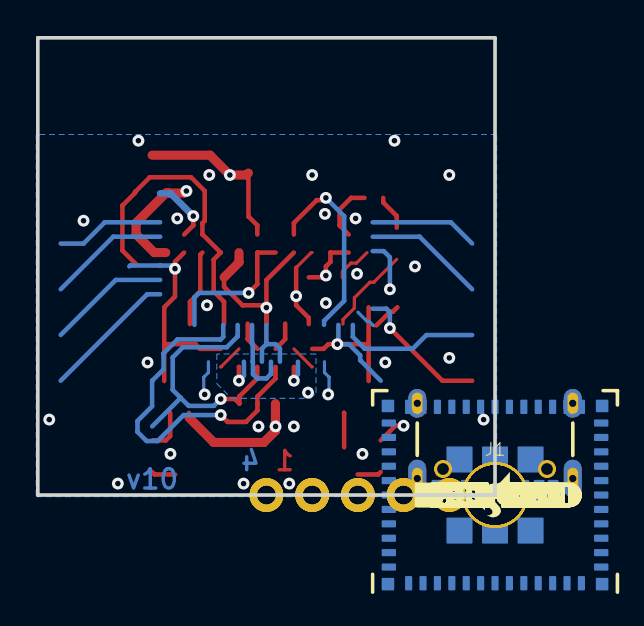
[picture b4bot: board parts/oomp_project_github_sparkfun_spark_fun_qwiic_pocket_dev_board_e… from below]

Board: 4 copper layers, 25.4 x 25.4 mm, 96 parts (23 on the bottom side), 35 nets.

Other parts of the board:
U$1: #_GND#0
U$2: #_3V3#0
U$3: #V3_#0
U$5: #GND_#0
U$6: SFE_LOGO_FLAME_.2
U$7: #VU_#0
U$8: #_VB#0
U$9, U$25: QWIIC_DEV0
U$10: SFE_LOGO_FLAME_.1
U$11, U$12: ESP32#C633
U$13: #_IO5#0
U$14: #_IO4#0
U$15: #_IO3#0
U$16: #_IO2#0
U$17: #IO16_#0
U$18: #IO17_#0
U$19: #IO18_#0
U$20: #IO19_#0
U$21: #5_#0
U$22: #4_#0
U$23: #I�C#0
U$24: ORDERING_INSTRUCTIONS
U$26: #PWR#0
U$27: #SHLD#0
U$28: IO230
U$30: PWR0
U$31: #CHG#0
U$32: CHG0
U$33: BOOT0
U$34: RST0
U$35: IO90
U$36: #VB_#0
U$37: #_VU#0
U$38: #3_#0
U$39: #2_#0
U$40: #_16#0
U$41: #_17#0
U$42: #_18#0
U$43: #_19#0

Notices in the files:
parts/oomp_project_github_sparkfun_spark_fun_qwiic_led_stick_qwiic_led_stick_current/data/original/kicad_file.kicad_sch:
Released under the Creative Commons
https://creativecommons.org/licenses/by-sa/4.0
parts and their libraries:
Released under the Creative Commons Attribution Share-Alike 4.0 License
